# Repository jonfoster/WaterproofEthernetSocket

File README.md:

# WaterproofEthernetSocket
Waterproof Ethernet Socket - 3D print and PCBs

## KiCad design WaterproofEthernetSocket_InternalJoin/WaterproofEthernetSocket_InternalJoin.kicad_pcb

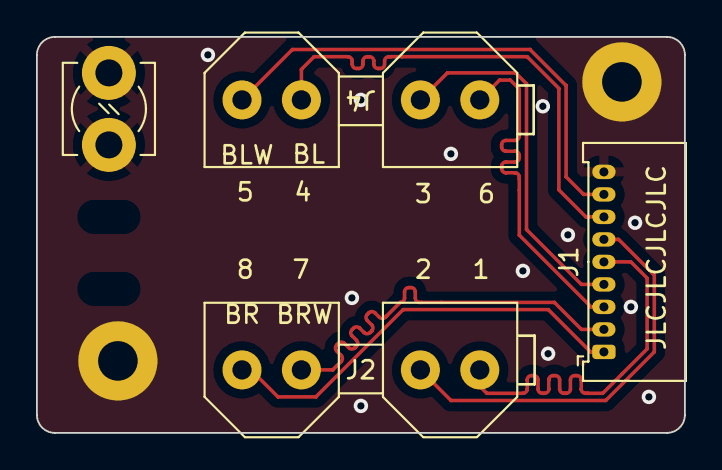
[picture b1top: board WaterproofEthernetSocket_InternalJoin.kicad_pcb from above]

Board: 2 copper layers, 36.0 x 22.0 mm, 6 parts (0 on the bottom side), 9 nets.

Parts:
H1, H2: MountingHole_Pad; MountingHole_2.2mm_M2_Pad
J1: Molex PicoBlade; Molex_PicoBlade_53048-0910_1x09_P1.25mm_Horizontal
J2: IDC Punch Down Block Half - Brown; Connector_IDC_8P_Cat6A_Stewart_SS-51000-003_Half
J3: Screw_Terminal_01x01; TerminalBlock_MetzConnect_360381_1x01_Horizontal_ScrewM3.0
J4: IDC Punch Down Block Half - Blue; Connector_IDC_8P_Cat6A_Stewart_SS-51000-003_Half

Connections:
/DA+: J1.5, J2.4
/DA-: J1.6, J2.3
/DB+: J1.4, J4.2
/DB-: J1.3, J4.1
/DC+: J1.7, J4.3
/DC-: J1.8, J4.4
/DD+: J1.2, J2.2
/DD-: J1.1, J2.1
GND: H1.1, H2.1, J1.9, J3.1

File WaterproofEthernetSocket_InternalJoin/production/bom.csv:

Designator,Footprint,Quantity,Value,LCSC Part #
"H1, H2",MountingHole_2.2mm_M2_Pad,2,MountingHole_Pad,
J1,Molex_PicoBlade_53048-0910_1x09_P1.25mm_Horizontal,1,Molex PicoBlade,
J2,Connector_IDC_8P_Cat6A_Stewart_SS-51000-003_Half,1,IDC Punch Down Block Half - Brown,SS-51000-004
J3,TerminalBlock_MetzConnect_360381_1x01_Horizontal_ScrewM3.0,1,Screw_Terminal_01x01,360381

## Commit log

2024-04-21 First version
2024-04-21 Ignore generated backup files
